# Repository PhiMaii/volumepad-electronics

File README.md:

# VolumePad STM32 PCB

Custom STM32-based PCB for the VolumePad project.

This board is intended for a haptic rotary input device with BLDC motor feedback, magnetic angle sensing, RGB LEDs, USB-C, buttons, strain sensing, and optional display support.

## Project status

Work in progress.

The current active development branch is `v2-redesign`.

The old version is kept on `v1-old`.

## Repository structure

    .
    ├── pcb/                 KiCad project files
    ├── docs/                Generated documentation, ignored by Git
    ├── fabrication/         Generated manufacturing files, ignored by Git
    ├── scripts/             Helper scripts
    ├── config.kibot.yaml    KiBot output configuration
    └── .github/workflows/   GitHub Actions automation

## PCB features

Planned / included hardware:

- STM32F405RGT6 microcontroller
- USB-C power and USB FS device connection
- TMC6300 BLDC motor driver
- MT6701 magnetic angle sensor
- WS2812B / SK6812 addressable RGB LEDs
- HX711-based strain sensing
- SWD programming connector
- Optional SPI display connection
- 4-layer PCB stackup

## KiCad project

Open the KiCad project from:

    open pcb/volumepad-stm32-pcb.kicad_pro

Main project files:

    pcb/volumepad-stm32-pcb.kicad_pro
    pcb/volumepad-stm32-pcb.kicad_sch
    pcb/volumepad-stm32-pcb.kicad_pcb

## KiBot automation

This repo uses KiBot through GitHub Actions to automatically generate documentation and manufacturing files.

Generated outputs include:

- Schematic PDF
- Gerber files
- Drill files
- BOM
- Pick-and-place position files

The workflow runs on changes to the PCB project or KiBot configuration.

Generated files are uploaded as GitHub Actions artifacts and are not committed to the repository.

## Generated files

Local generated outputs may appear in:

    docs/
    fabrication/

These files are intentionally ignored by Git.

## Notes

This PCB is still under active development and should not be considered production-ready yet.

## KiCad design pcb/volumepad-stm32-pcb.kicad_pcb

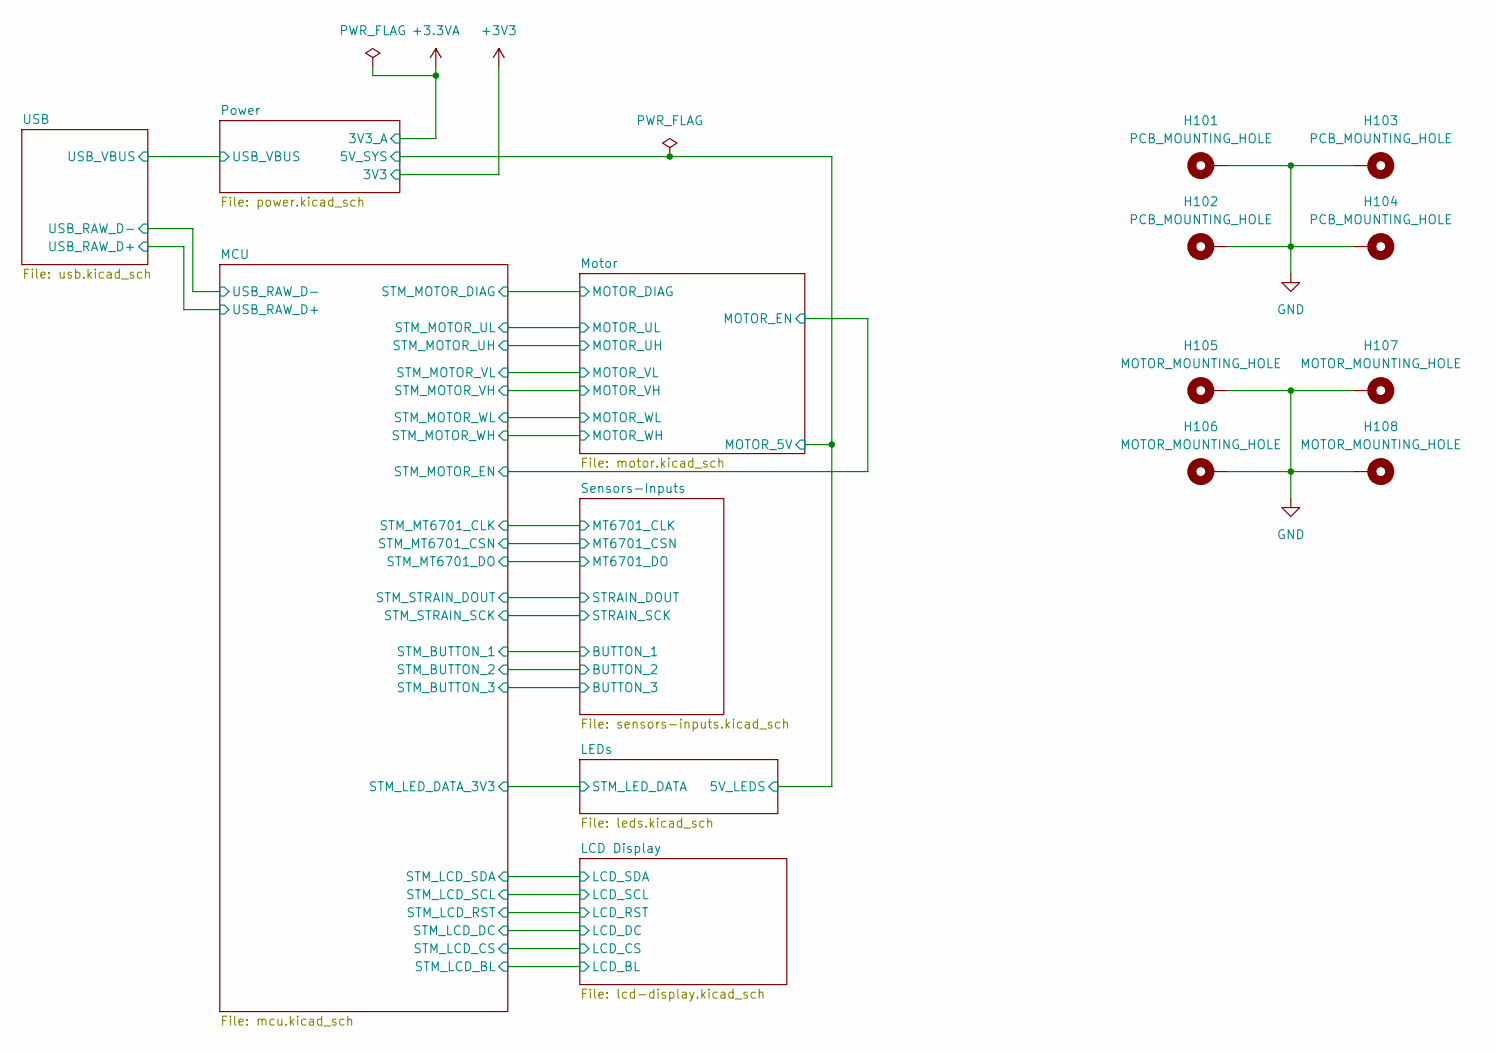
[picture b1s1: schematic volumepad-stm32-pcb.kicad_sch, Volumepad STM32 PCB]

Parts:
H101, H102, H103, H104: PCB_MOUNTING_HOLE; MountingHole_3mm_Pad_Via
H105, H106, H107, H108: MOTOR_MOUNTING_HOLE; MountingHole_2.5mm_Pad_Via

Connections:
GND: H101.1 (1_1), H102.1 (1_1), H103.1 (1_1), H104.1 (1_1), H105.1 (1_1), H106.1 (1_1), H107.1 (1_1), H108.1 (1_1); also elsewhere on the board

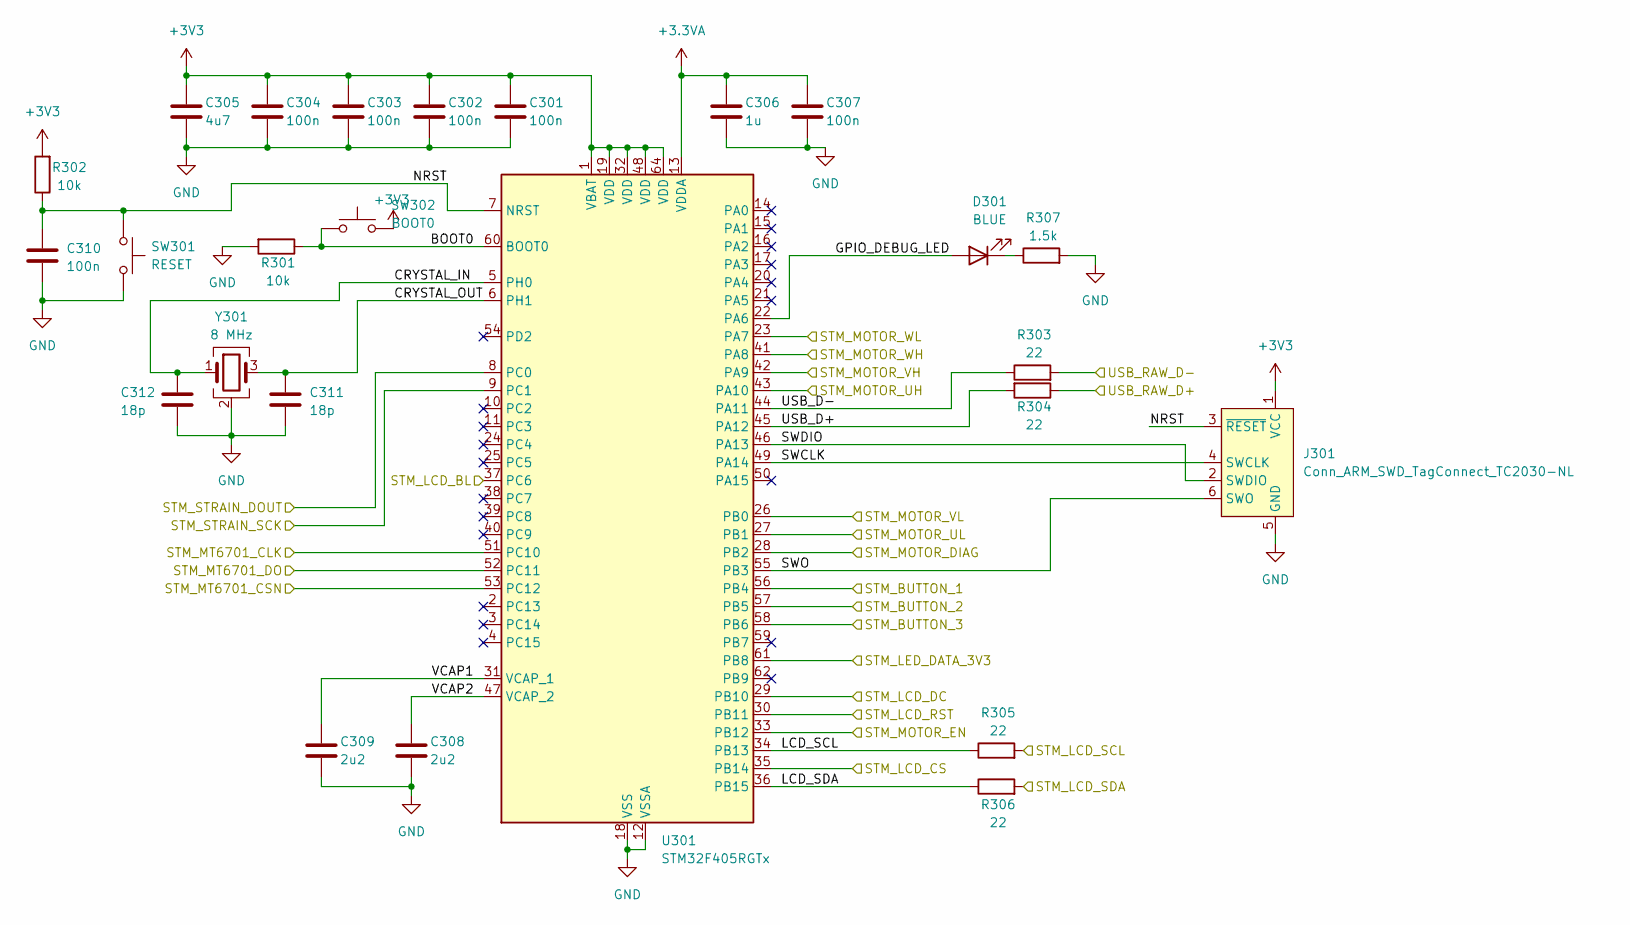
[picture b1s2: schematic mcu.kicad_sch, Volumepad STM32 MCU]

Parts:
C301, C302, C303, C304, C307, C310: 100n; C_0603_1608Metric
C305: 4u7; C_0805_2012Metric
C306: 1u; C_0603_1608Metric
C308, C309: 2u2; C_0805_2012Metric
C311, C312: 18p; C_0603_1608Metric
D301: BLUE; LED_0603_1608Metric
J301: Conn_ARM_SWD_TagConnect_TC2030-NL; Tag-Connect_TC2030-IDC-NL_2x03_P1.27mm_Vertical
R301, R302: 10k; R_0603_1608Metric
R303, R304, R305, R306: 22; R_0603_1608Metric
R307: 1.5k; R_0603_1608Metric
SW301: RESET; SW_Push_SPST_NO_Alps_SKRK
SW302: BOOT0; SW_Push_SPST_NO_Alps_SKRK
U301: STM32F405RGTx; LQFP-64_10x10mm_P0.5mm
Y301: 8 MHz; Crystal_SMD_3225-4Pin_3.2x2.5mm

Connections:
+3.3VA: C306.1, C307.1, U301.13 (VDDA); also elsewhere on the board
+3V3: C301.1, C302.1, C303.1, C304.1, C305.1, J301.1 (VCC), R302.2, SW302.1, U301.1 (VBAT), U301.19 (VDD), U301.32 (VDD), U301.48 (VDD), U301.64 (VDD); also elsewhere on the board
/LCD Display/LCD_BL: U301.37 (PC6); also elsewhere on the board
/LCD Display/LCD_CS: U301.35 (PB14); also elsewhere on the board
/LCD Display/LCD_DC: U301.29 (PB10); also elsewhere on the board
/LCD Display/LCD_RST: U301.30 (PB11); also elsewhere on the board
/LCD Display/LCD_SCL: R305.2; also elsewhere on the board
/LCD Display/LCD_SDA: R306.2; also elsewhere on the board
/LEDs/STM_LED_DATA: U301.61 (PB8); also elsewhere on the board
/MCU/BOOT0: R301.1, SW302.2, U301.60 (BOOT0)
/MCU/CRYSTAL_IN: C312.2, U301.5 (PH0), Y301.1
/MCU/CRYSTAL_OUT: C311.1, U301.6 (PH1), Y301.3
/MCU/GPIO_DEBUG_LED: D301.2 (A), U301.22 (PA6)
/MCU/LCD_SCL: R305.1, U301.34 (PB13)
/MCU/LCD_SDA: R306.1, U301.36 (PB15)
/MCU/NRST: C310.1, J301.3 (~RESET), R302.1, SW301.1, U301.7 (NRST)
/MCU/STM_BUTTON_1: U301.56 (PB4); also elsewhere on the board
/MCU/STM_BUTTON_2: U301.57 (PB5); also elsewhere on the board
/MCU/STM_BUTTON_3: U301.58 (PB6); also elsewhere on the board
/MCU/STM_MOTOR_EN: U301.33 (PB12); also elsewhere on the board
/MCU/STM_MOTOR_UH: U301.43 (PA10); also elsewhere on the board
/MCU/STM_MOTOR_UL: U301.27 (PB1); also elsewhere on the board
/MCU/STM_MOTOR_VH: U301.42 (PA9); also elsewhere on the board
/MCU/STM_MOTOR_VL: U301.26 (PB0); also elsewhere on the board
/MCU/STM_MOTOR_WH: U301.41 (PA8); also elsewhere on the board
/MCU/STM_MOTOR_WL: U301.23 (PA7); also elsewhere on the board
/MCU/STM_MT6701_CLK: U301.51 (PC10); also elsewhere on the board
/MCU/STM_MT6701_CSN: U301.53 (PC12); also elsewhere on the board
/MCU/STM_MT6701_DO: U301.52 (PC11); also elsewhere on the board
/MCU/STM_STRAIN_DOUT: U301.8 (PC0); also elsewhere on the board
/MCU/STM_STRAIN_SCK: U301.9 (PC1); also elsewhere on the board
/MCU/SWCLK: J301.4 (SWCLK), U301.49 (PA14)
/MCU/SWDIO: J301.2 (SWDIO), U301.46 (PA13)
/MCU/SWO: J301.6 (SWO), U301.55 (PB3)
/MCU/USB_D+: R304.2, U301.45 (PA12)
/MCU/USB_D-: R303.1, U301.44 (PA11)
/MCU/USB_RAW_D+: R304.1; also elsewhere on the board
/MCU/USB_RAW_D-: R303.2; also elsewhere on the board
/MCU/VCAP1: C309.1, U301.31 (VCAP_1)
/MCU/VCAP2: C308.1, U301.47 (VCAP_2)
/Motor/MOTOR_DIAG: U301.28 (PB2); also elsewhere on the board
GND: C301.2, C302.2, C303.2, C304.2, C305.2, C306.2, C307.2, C308.2, C309.2, C310.2, C311.2, C312.1, J301.5 (GND), R301.2, R307.2, SW301.2, U301.12 (VSSA), U301.18 (VSS), U301.63 (VSS), Y301.2 (G), Y301.4 (G); also elsewhere on the board
unnamed: D301.1 (K), R307.1

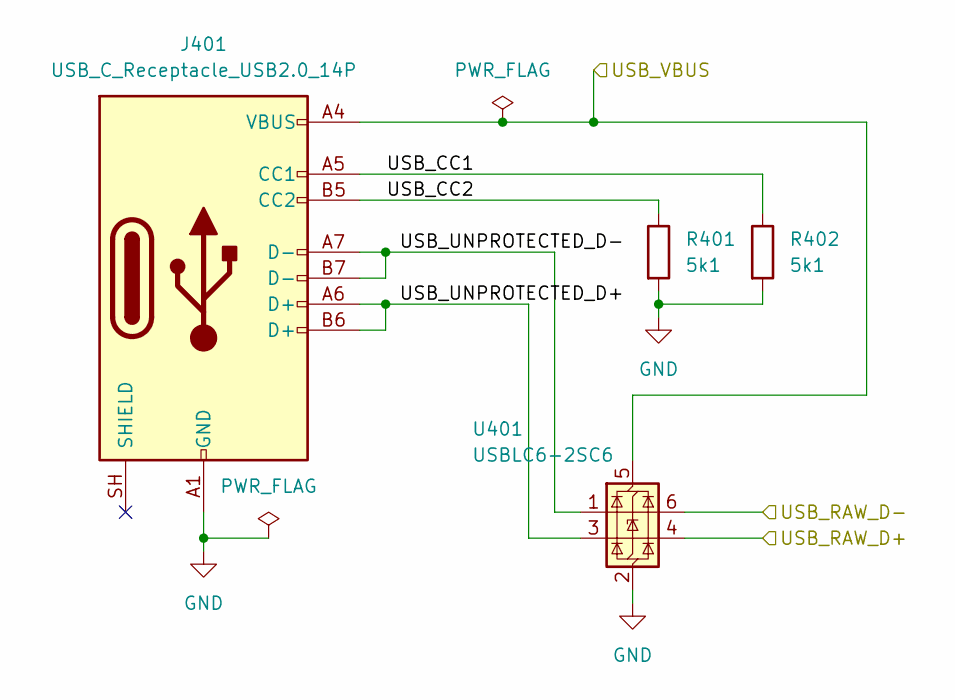
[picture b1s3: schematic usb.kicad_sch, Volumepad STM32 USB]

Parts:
J401: USB_C_Receptacle_USB2.0_14P; USB_C_Receptacle_GCT_USB4105-xx-A_16P_TopMnt_Horizontal
R401, R402: 5k1; R_0603_1608Metric
U401: USBLC6-2SC6; SOT-23-6

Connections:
/MCU/USB_RAW_D+: U401.4 (I/O2); also elsewhere on the board
/MCU/USB_RAW_D-: U401.6 (I/O1); also elsewhere on the board
/Power/USB_VBUS: J401.A4 (VBUS), J401.A9 (VBUS), J401.B4 (VBUS), J401.B9 (VBUS), U401.5 (VBUS); also elsewhere on the board
/USB/USB_CC1: J401.A5 (CC1), R402.1
/USB/USB_CC2: J401.B5 (CC2), R401.1
/USB/USB_UNPROTECTED_D+: J401.A6 (D+), J401.B6 (D+), U401.3 (I/O2)
/USB/USB_UNPROTECTED_D-: J401.A7 (D-), J401.B7 (D-), U401.1 (I/O1)
GND: J401.A1 (GND), J401.A12 (GND), J401.B1 (GND), J401.B12 (GND), R401.2, R402.2, U401.2 (GND); also elsewhere on the board

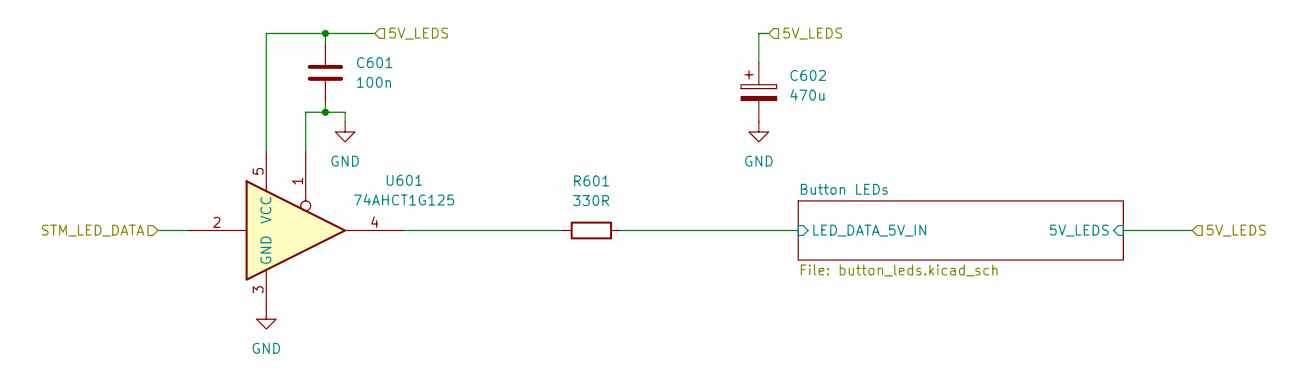
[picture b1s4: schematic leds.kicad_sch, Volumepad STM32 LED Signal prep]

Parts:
C601: 100n; C_0603_1608Metric; LCSC C42405541
C602: 470u; CP_Elec_6.3x5.8
R601: 330R; R_0603_1608Metric
U601: 74AHCT1G125; SOT-23-5

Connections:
/LEDs/Button LEDs/LED_DATA_5V_IN: R601.2; also elsewhere on the board
/LEDs/STM_LED_DATA: U601.2; also elsewhere on the board
/Power/5V_SYS: C601.1, C602.1, U601.5 (VCC); also elsewhere on the board
GND: C601.2, C602.2, U601.1, U601.3 (GND); also elsewhere on the board
unnamed: R601.1, U601.4

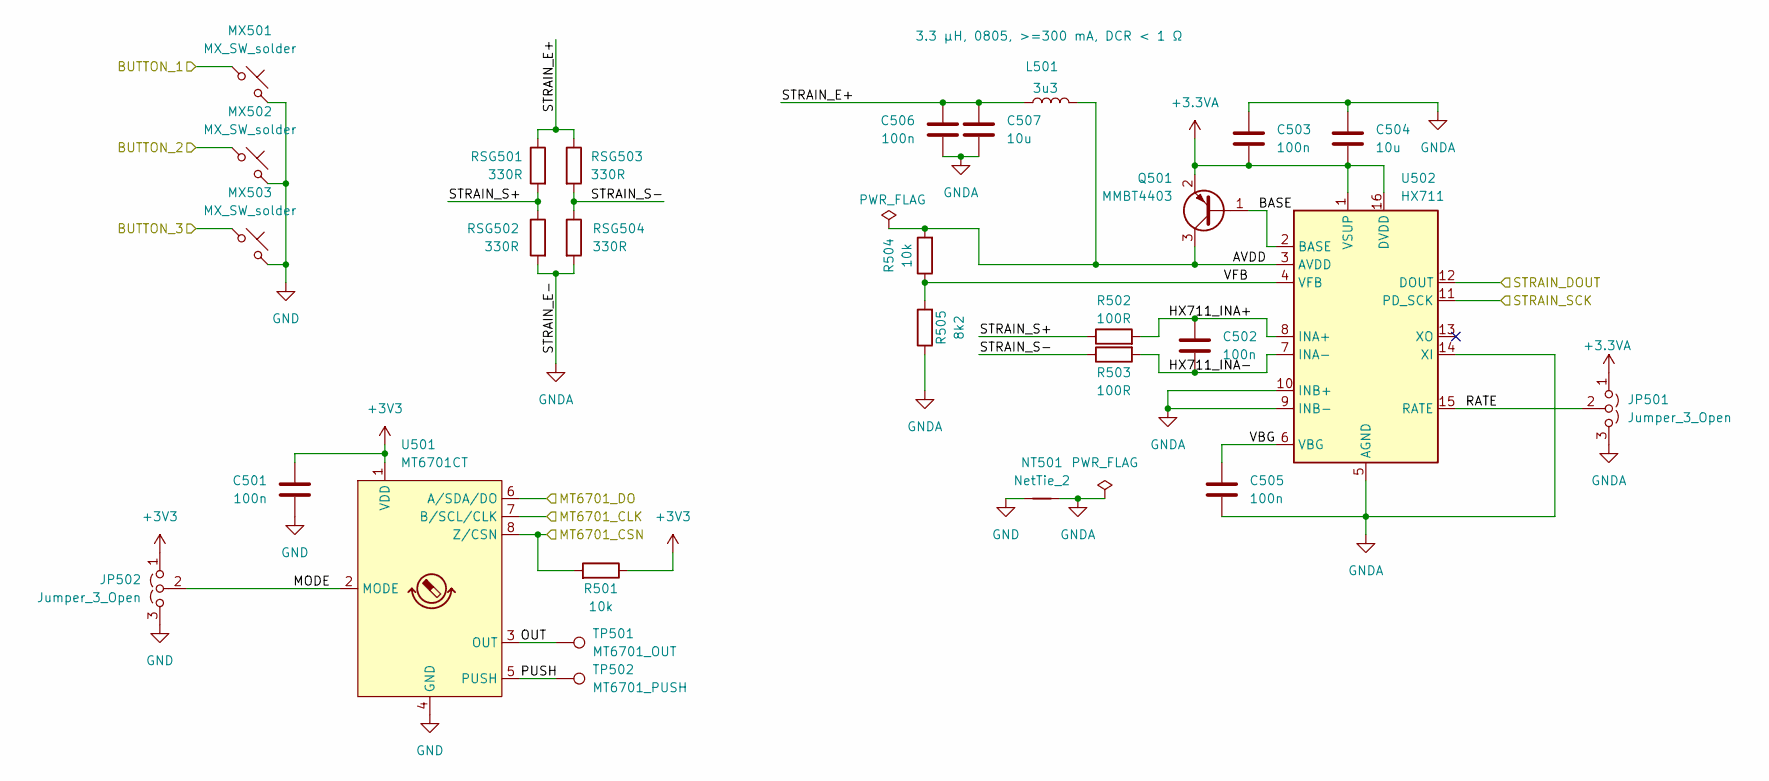
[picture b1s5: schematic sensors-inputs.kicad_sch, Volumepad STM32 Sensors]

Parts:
C501, C502, C503, C505, C506: 100n; C_0603_1608Metric; LCSC C42405541
C504, C507: 10u; C_0805_2012Metric
JP501, JP502: Jumper_3_Open; SolderJumper-3_P1.3mm_Open_RoundedPad1.0x1.5mm
L501: 3u3; L_0805_2012Metric
MX501, MX502, MX503: MX_SW_solder; SW_MX_1u
NT501: NetTie_2; NetTie-2_SMD_Pad0.5mm
Q501: MMBT4403; SOT-23
R501, R504: 10k; R_0603_1608Metric
R502, R503: 100R; R_0603_1608Metric
R505: 8k2; R_0603_1608Metric
RSG501, RSG502, RSG503, RSG504: 330R; R_2512_6332Metric
TP501: MT6701_OUT; TestPoint_Pad_D1.0mm
TP502: MT6701_PUSH; TestPoint_Pad_D1.0mm
U501: MT6701CT; SO-8_3.9x4.9mm_P1.27mm
U502: HX711; SOIC-16_3.9x9.9mm_P1.27mm

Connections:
+3.3VA: C503.2, C504.2, JP501.1 (A), Q501.2 (E), U502.1 (VSUP), U502.16 (DVDD); also elsewhere on the board
+3V3: C501.1, JP502.1 (A), R501.1, U501.1 (VDD); also elsewhere on the board
/MCU/STM_BUTTON_1: MX501.1; also elsewhere on the board
/MCU/STM_BUTTON_2: MX502.1; also elsewhere on the board
/MCU/STM_BUTTON_3: MX503.1; also elsewhere on the board
/MCU/STM_MT6701_CLK: U501.7 (B/SCL/CLK); also elsewhere on the board
/MCU/STM_MT6701_CSN: R501.2, U501.8 (Z/CSN); also elsewhere on the board
/MCU/STM_MT6701_DO: U501.6 (A/SDA/DO); also elsewhere on the board
/MCU/STM_STRAIN_DOUT: U502.12 (DOUT); also elsewhere on the board
/MCU/STM_STRAIN_SCK: U502.11 (PD_SCK); also elsewhere on the board
/Sensors-Inputs/AVDD: L501.1, Q501.3 (C), R504.2, U502.3 (AVDD)
/Sensors-Inputs/BASE: Q501.1 (B), U502.2 (BASE)
/Sensors-Inputs/HX711_INA+: C502.1, R502.2, U502.8 (INA+)
/Sensors-Inputs/HX711_INA-: C502.2, R503.2, U502.7 (INA-)
/Sensors-Inputs/MODE: JP502.2 (C), U501.2 (MODE)
/Sensors-Inputs/OUT: TP501.1 (1_1), U501.3 (OUT)
/Sensors-Inputs/PUSH: TP502.1 (1_1), U501.5 (PUSH)
/Sensors-Inputs/RATE: JP501.2 (C), U502.15 (RATE)
/Sensors-Inputs/STRAIN_E+: C506.1, C507.1, L501.2, RSG501.1, RSG503.1
/Sensors-Inputs/STRAIN_S+: R502.1, RSG501.2, RSG502.1
/Sensors-Inputs/STRAIN_S-: R503.1, RSG503.2, RSG504.1
/Sensors-Inputs/VBG: C505.1, U502.6 (VBG)
/Sensors-Inputs/VFB: R504.1, R505.2, U502.4 (VFB)
GND: C501.2, JP502.3 (B), MX501.2, MX502.2, MX503.2, NT501.1, U501.4 (GND); also elsewhere on the board
GNDA: C503.1, C504.1, C505.2, C506.2, C507.2, JP501.3 (B), NT501.2, R505.1, RSG502.2, RSG504.2, U502.5 (AGND), U502.9 (INB-), U502.10 (INB+), U502.14 (XI)

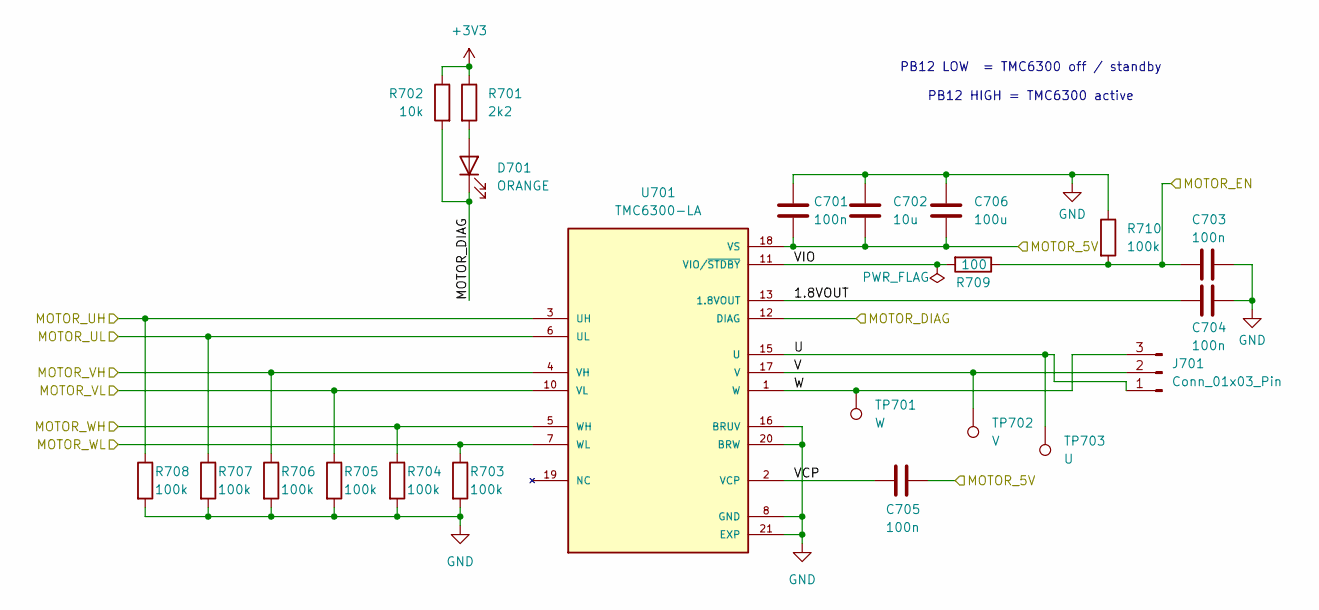
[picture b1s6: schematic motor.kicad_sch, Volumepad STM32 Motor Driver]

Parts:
C701, C703, C704, C705: 100n; C_0603_1608Metric
C702: 10u; C_0805_2012Metric
C706: 100u; CP_Elec_5x5.8
D701: ORANGE; LED_0603_1608Metric
J701: Conn_01x03_Pin; JST_SH_SM03B-SRSS-TB_1x03-1MP_P1.00mm_Horizontal
R701: 2k2; R_0603_1608Metric
R702: 10k; R_0603_1608Metric
R703, R704, R705, R706, R707, R708, R710: 100k; R_0603_1608Metric
R709: 100; R_0603_1608Metric
TP701: W; TestPoint_Pad_D1.0mm
TP702: V; TestPoint_Pad_D1.0mm
TP703: U; TestPoint_Pad_D1.0mm
U701: TMC6300-LA; QFN40P300X300X90-21N; PARTREV 1.08

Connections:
+3V3: R701.1, R702.1; also elsewhere on the board
/MCU/STM_MOTOR_EN: C703.1, R709.1, R710.2; also elsewhere on the board
/MCU/STM_MOTOR_UH: R708.1, U701.3 (UH); also elsewhere on the board
/MCU/STM_MOTOR_UL: R707.1, U701.6 (UL); also elsewhere on the board
/MCU/STM_MOTOR_VH: R706.1, U701.4 (VH); also elsewhere on the board
/MCU/STM_MOTOR_VL: R705.1, U701.10 (VL); also elsewhere on the board
/MCU/STM_MOTOR_WH: R704.1, U701.5 (WH); also elsewhere on the board
/MCU/STM_MOTOR_WL: R703.1, U701.7 (WL); also elsewhere on the board
/Motor/1.8VOUT: C704.2, U701.13 (1.8VOUT)
/Motor/MOTOR_DIAG: D701.1 (K), R702.2, U701.12 (DIAG); also elsewhere on the board
/Motor/U: J701.1, TP703.1 (1_1), U701.15 (U)
/Motor/V: J701.2, TP702.1 (1_1), U701.17 (V)
/Motor/VCP: C705.1, U701.2 (VCP)
/Motor/VIO: R709.2, U701.11 (VIO/~STDBY)
/Motor/W: J701.3, TP701.1 (1_1), U701.1 (W)
/Power/5V_SYS: C701.2, C702.2, C705.2, C706.2, U701.18 (VS); also elsewhere on the board
GND: C701.1, C702.1, C703.2, C704.1, C706.1, R703.2, R704.2, R705.2, R706.2, R707.2, R708.2, R710.1, U701.8 (GND), U701.9 (GND), U701.14 (GND), U701.16 (BRUV), U701.20 (BRW), U701.21 (EXP); also elsewhere on the board
unnamed: D701.2 (A), R701.2

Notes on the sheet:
PB12 LOW = TMC6300 off / standby PB12 HIGH = TMC6300 active

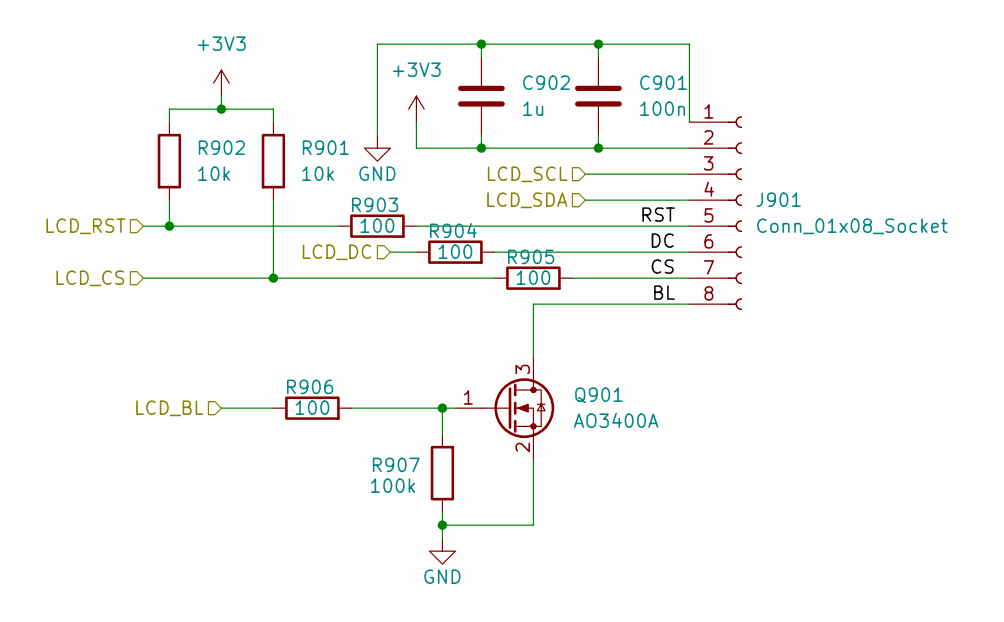
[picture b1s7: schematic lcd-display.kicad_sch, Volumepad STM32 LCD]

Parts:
C901: 100n; C_0603_1608Metric
C902: 1u; C_0603_1608Metric
J901: Conn_01x08_Socket; PinHeader_1x08_P2.54mm_Vertical
Q901: AO3400A; SOT-23
R901, R902: 10k; R_0603_1608Metric
R903, R904, R905, R906: 100; R_0603_1608Metric
R907: 100k; R_0603_1608Metric

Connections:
+3V3: C901.2, C902.2, J901.2 (VCC), R901.1, R902.1; also elsewhere on the board
/LCD Display/BL: J901.8 (BL), Q901.3 (D)
/LCD Display/CS: J901.7 (CS), R905.2
/LCD Display/DC: J901.6 (DC), R904.2
/LCD Display/LCD_BL: R906.1; also elsewhere on the board
/LCD Display/LCD_CS: R901.2, R905.1; also elsewhere on the board
/LCD Display/LCD_DC: R904.1; also elsewhere on the board
/LCD Display/LCD_RST: R902.2, R903.1; also elsewhere on the board
/LCD Display/LCD_SCL: J901.3 (SCL); also elsewhere on the board
/LCD Display/LCD_SDA: J901.4 (SDA); also elsewhere on the board
/LCD Display/RST: J901.5 (RST), R903.2
GND: C901.1, C902.1, J901.1 (GND), Q901.2 (S), R907.1; also elsewhere on the board
unnamed: Q901.1 (G), R906.2, R907.2

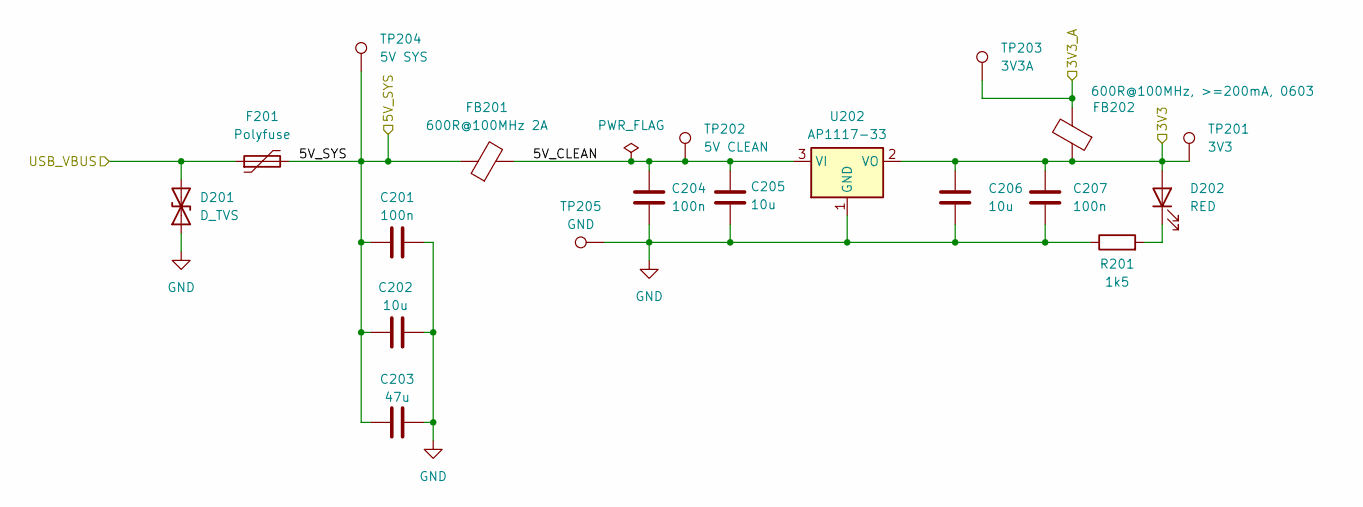
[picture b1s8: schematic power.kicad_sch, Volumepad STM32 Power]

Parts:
C201, C204, C207: 100n; C_0603_1608Metric; LCSC C42405541
C202, C205, C206: 10u; C_0805_2012Metric
C203: 47u; C_1206_3216Metric
D201: D_TVS; D_SOD-123; LCSC C2445454
D202: RED; LED_0603_1608Metric
F201: Polyfuse; Fuse_1206_3216Metric; LCSC Part # C70082
FB201: 600R@100MHz 2A; L_0805_2012Metric
FB202: 600R@100MHz, >=200mA, 0603; L_0603_1608Metric
R201: 1k5; R_0603_1608Metric
TP201: 3V3; TestPoint_Pad_D1.0mm
TP202: 5V CLEAN; TestPoint_Pad_D1.0mm
TP203: 3V3A; TestPoint_Pad_D1.0mm
TP204: 5V SYS; TestPoint_Pad_D1.0mm
TP205: GND; TestPoint_Pad_D1.0mm
U202: AP1117-33; SOT-223-3_TabPin2

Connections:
+3.3VA: FB202.2, TP203.1 (1_1); also elsewhere on the board
+3V3: C206.1, C207.2, D202.2 (A), FB202.1, TP201.1 (1_1), U202.2 (VO); also elsewhere on the board
/Power/5V_CLEAN: C204.1, C205.2, FB201.2, TP202.1 (1_1), U202.3 (VI)
/Power/5V_SYS: C201.1, C202.2, C203.2, F201.2, FB201.1, TP204.1 (1_1); also elsewhere on the board
/Power/USB_VBUS: D201.2 (A2), F201.1; also elsewhere on the board
GND: C201.2, C202.1, C203.1, C204.2, C205.1, C206.2, C207.1, D201.1 (A1), R201.1, TP205.1 (1_1), U202.1 (GND); also elsewhere on the board
unnamed: D202.1 (K), R201.2

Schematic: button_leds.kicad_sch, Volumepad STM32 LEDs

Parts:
C801, C802, C803, C804, C805, C806, C807, C808, C809, C810, C811, C812, C813: 100n; C_0603_1608Metric; LCSC C42405541
C814, C815, C816, C817, C818, C819, C820, C821, C822, C823, C824, C825, C826, C827, C828, C829, C830, C831, C832, C833, C834, C835: 100n; C_0603_1608Metric
D804, D805, D806, D807, D808, D809, D810, D811, D812, D813, D814, D815, D816, D817, D818, D819, D820, D821, D822, D823, D824, D825, D826, D827, D828, D829, D830, D831, D832, D833, D834, D835: WS2812B-2020; LED_WS2812B-2020_PLCC4_2.0x2.0mm
LED801, LED802, LED803: MX_SK6812MINI-E; LED_MX_6028R

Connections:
/LEDs/Button LEDs/LED_DATA_5V_IN: LED801.3 (DIN); also elsewhere on the board
/LEDs/Button LEDs/LED_DATA_5V_OUT: D804.3 (DIN), LED803.2 (DOUT)
/Power/5V_SYS: C801.1, C802.1, C803.1, C804.1, C805.1, C806.1, C807.1, C808.1, C809.1, C810.1, C811.1, C812.1, C813.1, C814.1, C815.1, C816.1, C817.1, C818.1, C819.1, C820.1, C821.1, C822.1, C823.1, C824.1, C825.1, C826.1, C827.1, C828.1, C829.1, C830.1, C831.1, C832.1, C833.1, C834.1, C835.1, D804.4 (VDD), D805.4 (VDD), D806.4 (VDD), D807.4 (VDD), D808.4 (VDD), D809.4 (VDD), D810.4 (VDD), D811.4 (VDD), D812.4 (VDD), D813.4 (VDD), D814.4 (VDD), D815.4 (VDD), D816.4 (VDD), D817.4 (VDD), D818.4 (VDD), D819.4 (VDD), D820.4 (VDD), D821.4 (VDD), D822.4 (VDD), D823.4 (VDD), D824.4 (VDD), D825.4 (VDD), D826.4 (VDD), D827.4 (VDD), D828.4 (VDD), D829.4 (VDD), D830.4 (VDD), D831.4 (VDD), D832.4 (VDD), D833.4 (VDD), D834.4 (VDD), D835.4 (VDD), LED801.1 (VDD), LED802.1 (VDD), LED803.1 (VDD); also elsewhere on the board
GND: C801.2, C802.2, C803.2, C804.2, C805.2, C806.2, C807.2, C808.2, C809.2, C810.2, C811.2, C812.2, C813.2, C814.2, C815.2, C816.2, C817.2, C818.2, C819.2, C820.2, C821.2, C822.2, C823.2, C824.2, C825.2, C826.2, C827.2, C828.2, C829.2, C830.2, C831.2, C832.2, C833.2, C834.2, C835.2, D804.2 (VSS), D805.2 (VSS), D806.2 (VSS), D807.2 (VSS), D808.2 (VSS), D809.2 (VSS), D810.2 (VSS), D811.2 (VSS), D812.2 (VSS), D813.2 (VSS), D814.2 (VSS), D815.2 (VSS), D816.2 (VSS), D817.2 (VSS), D818.2 (VSS), D819.2 (VSS), D820.2 (VSS), D821.2 (VSS), D822.2 (VSS), D823.2 (VSS), D824.2 (VSS), D825.2 (VSS), D826.2 (VSS), D827.2 (VSS), D828.2 (VSS), D829.2 (VSS), D830.2 (VSS), D831.2 (VSS), D832.2 (VSS), D833.2 (VSS), D834.2 (VSS), D835.2 (VSS), LED801.4 (VSS), LED802.4 (VSS), LED803.4 (VSS); also elsewhere on the board
unnamed: D804.1 (DOUT), D805.3 (DIN)
unnamed: D805.1 (DOUT), D806.3 (DIN)
unnamed: D806.1 (DOUT), D807.3 (DIN)
unnamed: D807.1 (DOUT), D808.3 (DIN)
unnamed: D808.1 (DOUT), D809.3 (DIN)
unnamed: D809.1 (DOUT), D810.3 (DIN)
unnamed: D810.1 (DOUT), D811.3 (DIN)
unnamed: D811.1 (DOUT), D812.3 (DIN)
unnamed: D812.1 (DOUT), D813.3 (DIN)
unnamed: D813.1 (DOUT), D814.3 (DIN)
unnamed: D814.1 (DOUT), D815.3 (DIN)
unnamed: D815.1 (DOUT), D816.3 (DIN)
unnamed: D816.1 (DOUT), D817.3 (DIN)
unnamed: D817.1 (DOUT), D818.3 (DIN)
unnamed: D818.1 (DOUT), D819.3 (DIN)
unnamed: D819.1 (DOUT), D820.3 (DIN)
unnamed: D820.1 (DOUT), D821.3 (DIN)
unnamed: D821.1 (DOUT), D822.3 (DIN)
unnamed: D822.1 (DOUT), D823.3 (DIN)
unnamed: D823.1 (DOUT), D824.3 (DIN)
unnamed: D824.1 (DOUT), D825.3 (DIN)
unnamed: D825.1 (DOUT), D826.3 (DIN)
unnamed: D826.1 (DOUT), D827.3 (DIN)
unnamed: D827.1 (DOUT), D828.3 (DIN)
unnamed: D828.1 (DOUT), D829.3 (DIN)
unnamed: D829.1 (DOUT), D830.3 (DIN)
unnamed: D830.1 (DOUT), D831.3 (DIN)
unnamed: D831.1 (DOUT), D832.3 (DIN)
unnamed: D832.1 (DOUT), D833.3 (DIN)
unnamed: D833.1 (DOUT), D834.3 (DIN)
unnamed: D834.1 (DOUT), D835.3 (DIN)
unnamed: LED801.2 (DOUT), LED802.3 (DIN)
unnamed: LED802.2 (DOUT), LED803.3 (DIN)

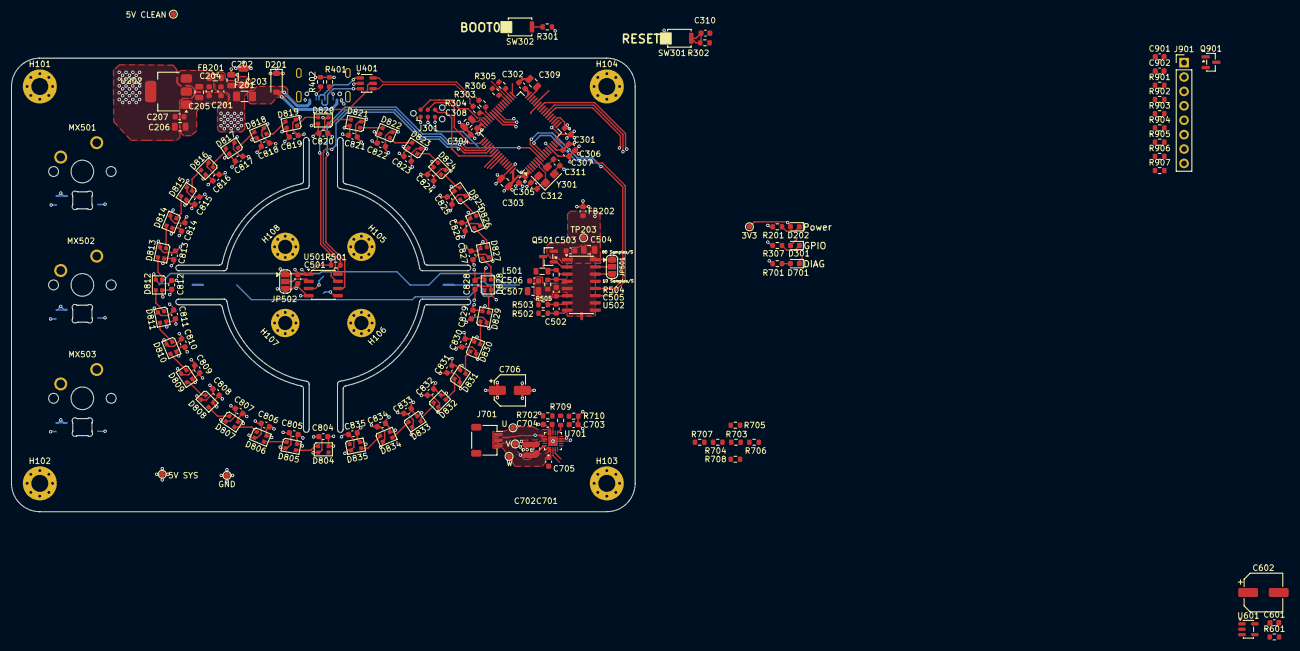
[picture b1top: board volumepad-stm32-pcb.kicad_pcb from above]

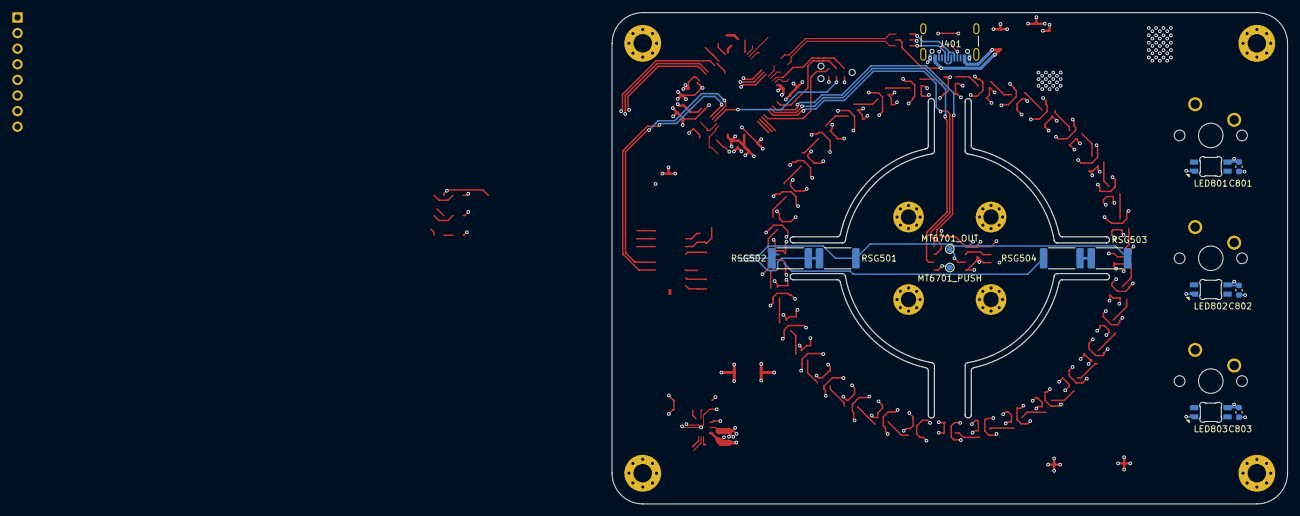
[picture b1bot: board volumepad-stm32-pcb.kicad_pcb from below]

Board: 4 copper layers, 110.0 x 80.0 mm, 191 parts (13 on the bottom side), 113 nets.
